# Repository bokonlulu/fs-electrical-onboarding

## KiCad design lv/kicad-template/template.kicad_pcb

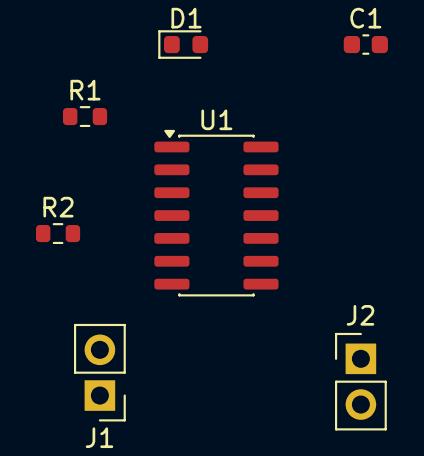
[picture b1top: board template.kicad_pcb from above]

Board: 2 copper layers, 7 parts (0 on the bottom side), 5 nets, no tracks yet.

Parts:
C1: 10mf; C_0603_1608Metric
D1: D_Small; D_0603_1608Metric
J1, J2: Conn_01x02; PinHeader_1x02_P2.54mm_Vertical
R1: 24k; R_0603_1608Metric
R2: 1k; R_0603_1608Metric
U1: MCP6004; SOIC-14_3.9x8.7mm_P1.27mm

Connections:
/PK_HOLD_VAL: J2.1, U1.6 (-), U1.7
GND: C1.2, J1.1, J2.2, R2.2
unnamed: C1.1, D1.1 (K_1), U1.2 (-), U1.5 (+)
unnamed: J1.2, R1.1
unnamed: R1.2, R2.1, U1.3 (+)
